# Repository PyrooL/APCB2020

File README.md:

# Advent of PCBs 2020
PCB design advent calendar: doing a design every [few] day[s]!

3 - RGB sensor using 3 photoresistors and filter paper, on an ATTiny85

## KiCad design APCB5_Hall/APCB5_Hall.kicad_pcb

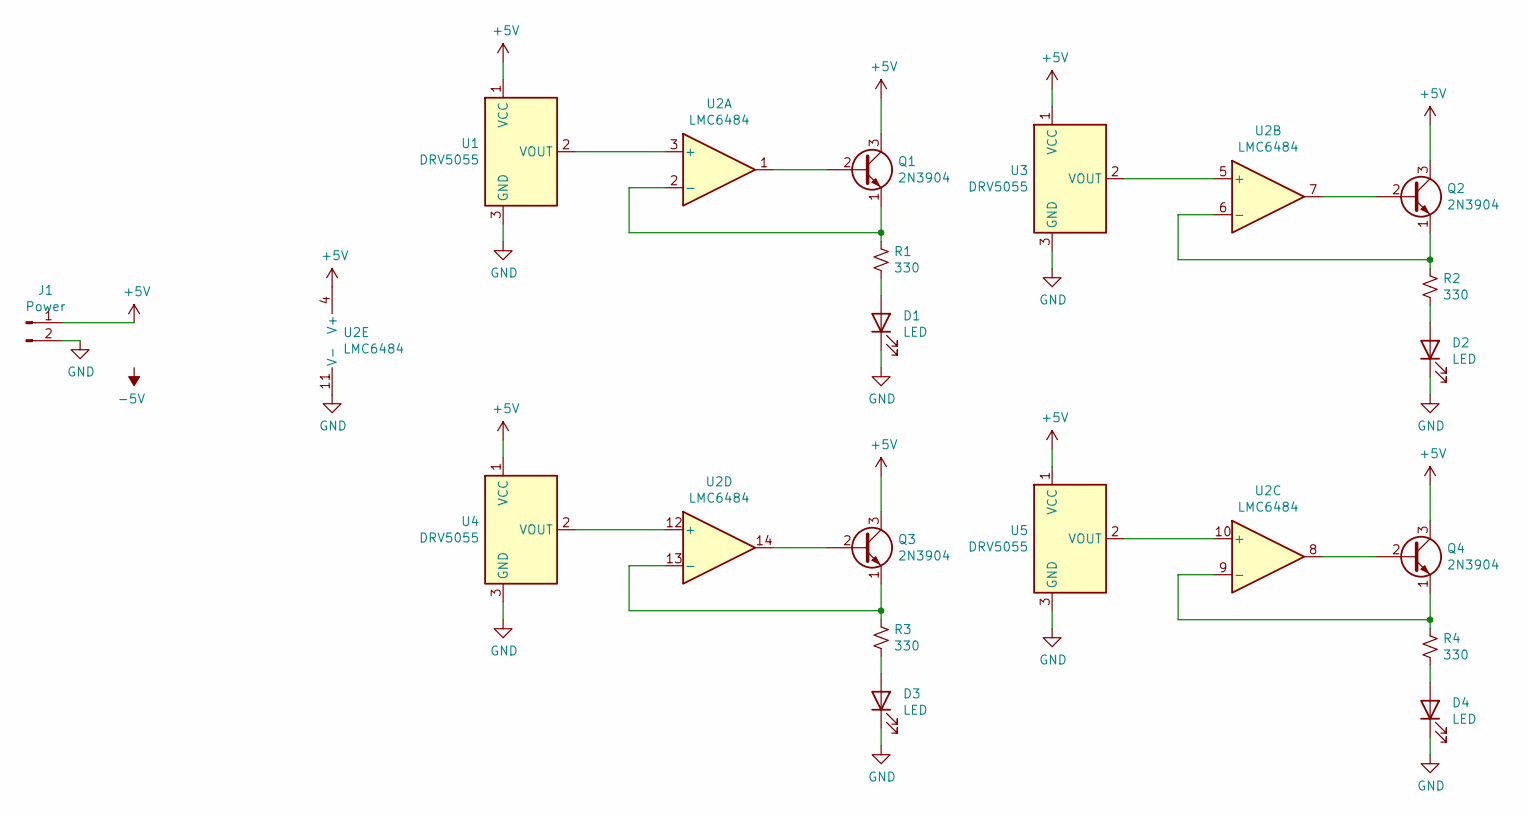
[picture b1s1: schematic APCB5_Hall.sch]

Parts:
D1, D2, D3, D4: LED; LED_1206_3216Metric
J1: Power; PinHeader_1x02_P2.54mm_Vertical
Q1, Q2, Q3, Q4: 2N3904; TO-92_Inline
R1, R2, R3, R4: 330; R_0805_2012Metric
U1, U3, U4, U5: DRV5055; SOT-23
U2: LMC6484; SOIC-14_3.9x8.7mm_P1.27mm

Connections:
+5V: J1.1, Q1.3 (C), Q2.3 (C), Q3.3 (C), Q4.3 (C), U1.1 (VCC), U2.4 (V+), U3.1 (VCC), U4.1 (VCC), U5.1 (VCC)
GND: D1.1 (K), D2.1 (K), D3.1 (K), D4.1 (K), J1.2, U1.3 (GND), U2.11 (V-), U3.3 (GND), U4.3 (GND), U5.3 (GND)
unnamed: D1.2 (A), R1.2
unnamed: D2.2 (A), R2.2
unnamed: D3.2 (A), R3.2
unnamed: D4.2 (A), R4.2
unnamed: Q1.1 (E), R1.1, U2.2 (-)
unnamed: Q1.2 (B), U2.1
unnamed: Q2.1 (E), R2.1, U2.6 (-)
unnamed: Q2.2 (B), U2.7
unnamed: Q3.1 (E), R3.1, U2.13 (-)
unnamed: Q3.2 (B), U2.14
unnamed: Q4.1 (E), R4.1, U2.9 (-)
unnamed: Q4.2 (B), U2.8
unnamed: U1.2 (VOUT), U2.3 (+)
unnamed: U2.5 (+), U3.2 (VOUT)
unnamed: U2.10 (+), U5.2 (VOUT)
unnamed: U2.12 (+), U4.2 (VOUT)

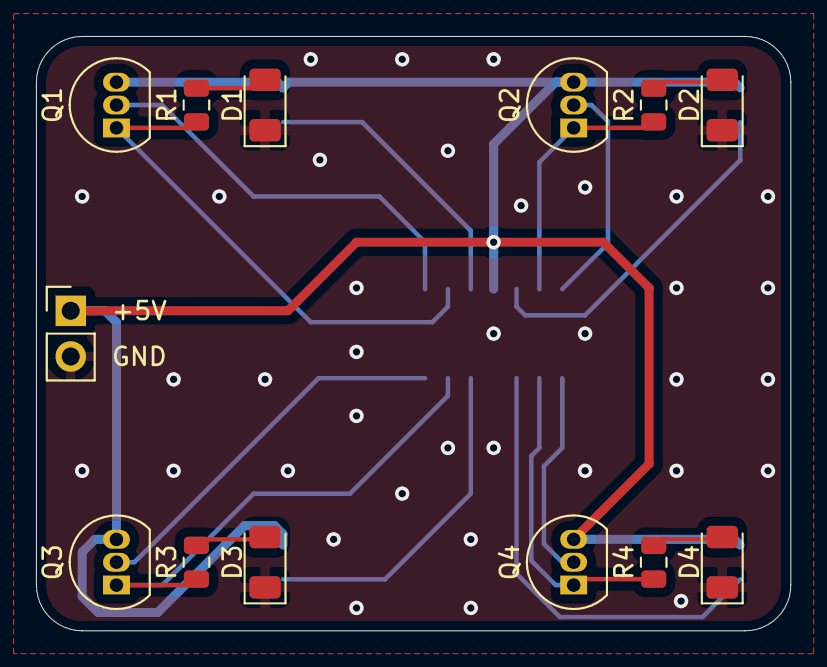
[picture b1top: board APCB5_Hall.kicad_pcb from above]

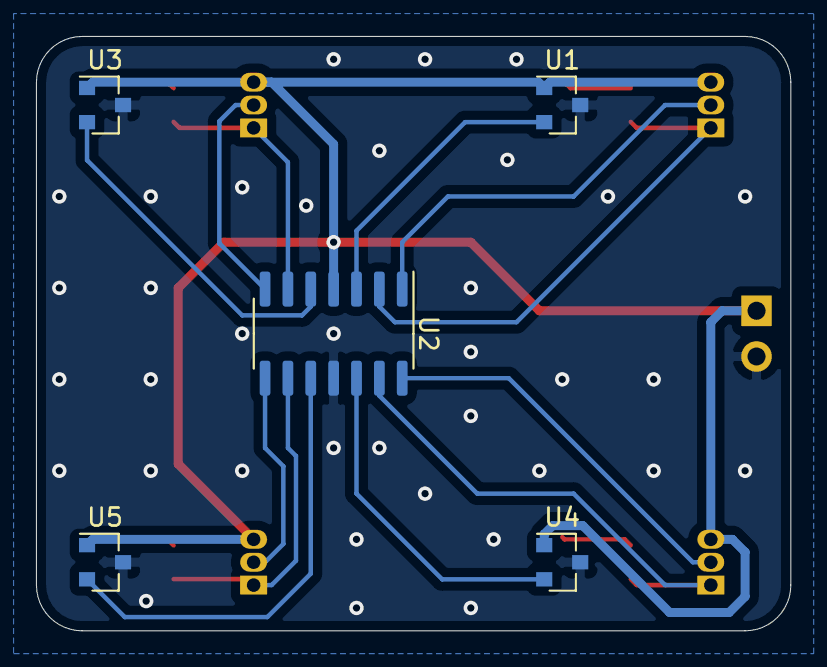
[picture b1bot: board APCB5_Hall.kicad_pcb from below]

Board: 2 copper layers, 41.9 x 33.0 mm, 18 parts (5 on the bottom side), 18 nets.

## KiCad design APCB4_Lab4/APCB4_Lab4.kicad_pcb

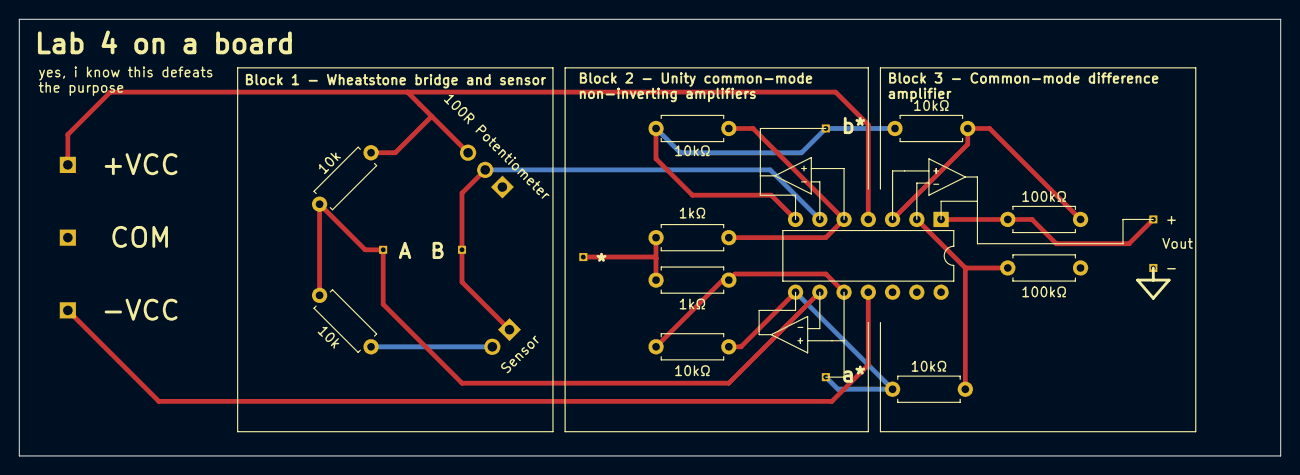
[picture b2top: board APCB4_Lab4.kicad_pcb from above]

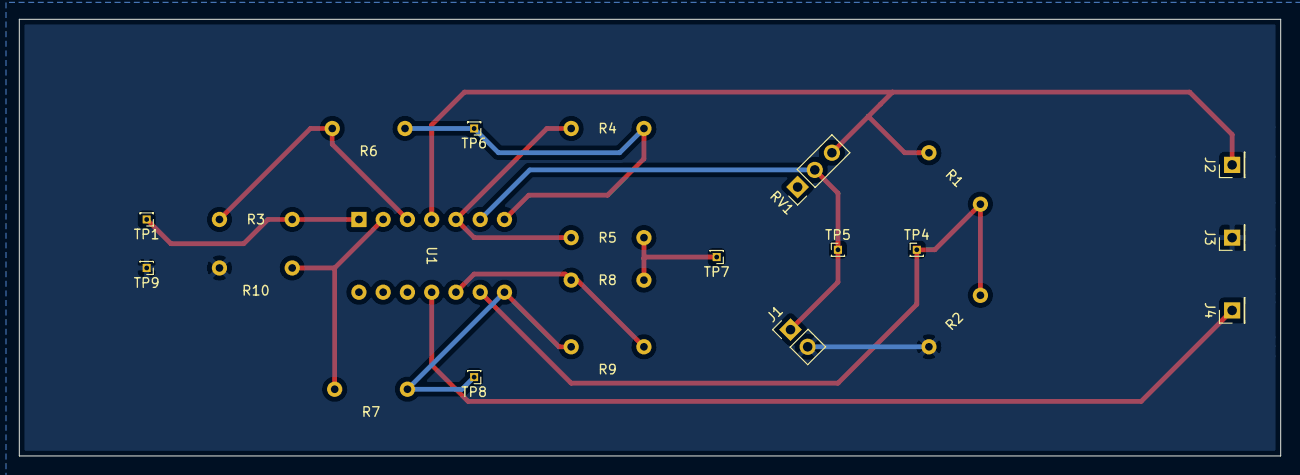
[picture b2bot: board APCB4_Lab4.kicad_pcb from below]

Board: 2 copper layers, 132.1 x 45.7 mm, 23 parts (12 on the bottom side), 13 nets.

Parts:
J1: Sensor; PinHeader_1x02_P2.54mm_Vertical
J2, J3, J4: Conn_01x01_Female; PinHeader_1x01_P2.54mm_Vertical
R1, R2: 10k; R_Axial_DIN0207_L6.3mm_D2.5mm_P7.62mm_Horizontal
R3, R10: 100kΩ; R_Axial_DIN0207_L6.3mm_D2.5mm_P7.62mm_Horizontal
R4, R6, R7, R9: 10kΩ; R_Axial_DIN0207_L6.3mm_D2.5mm_P7.62mm_Horizontal
R5, R8: 1kΩ; R_Axial_DIN0207_L6.3mm_D2.5mm_P7.62mm_Horizontal
RV1: 100R Potentiometer; PinHeader_1x03_P2.54mm_Vertical
TP1, TP4, TP5, TP6, TP7, TP8, TP9: TestPoint; PinHeader_1x01_P1.00mm_Vertical
U1: LMC6484; DIP-14_W7.62mm

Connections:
+VDC: J2.1, R1.1, RV1.3, U1.4
-VDC: J4.1, U1.11
/*: R5.1, R8.2, TP7.1
/A: R1.2, R2.1, TP4.1, U1.9
/B: J1.1, RV1.2, TP5.1, U1.6
/Vout: R3.2, TP1.1, U1.1
/a*: R7.2, R9.1, TP8.1, U1.8
/b*: R4.1, R6.2, TP6.1, U1.7
GND: J1.2, J3.1, R2.2, R10.1, TP9.1
unnamed: R3.1, R6.1, U1.3
unnamed: R4.2, R5.2, U1.5
unnamed: R8.1, R9.2, U1.10
unnamed: R7.1, R10.2, U1.2

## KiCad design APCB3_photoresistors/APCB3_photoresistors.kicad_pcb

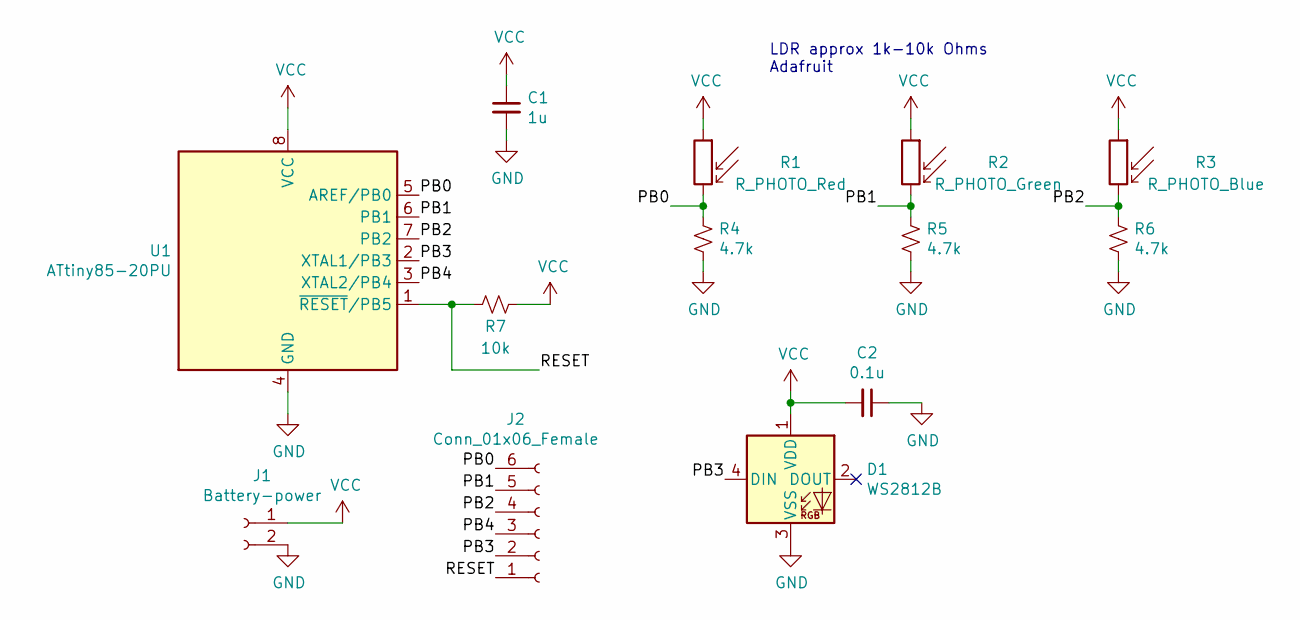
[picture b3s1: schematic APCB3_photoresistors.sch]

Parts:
C1: 1u; C_0805_2012Metric
C2: 0.1u; C_0805_2012Metric
D1: WS2812B; LED_WS2812B_PLCC4_5.0x5.0mm_P3.2mm
J1: Battery-power; PinHeader_1x02_P2.54mm_Vertical
J2: Conn_01x06_Female; PinHeader_1x06_P2.54mm_Vertical
R1: R_PHOTO_Red; R_LDR_5.1x4.3mm_P3.4mm_Vertical
R2: R_PHOTO_Green; R_LDR_5.1x4.3mm_P3.4mm_Vertical
R3: R_PHOTO_Blue; R_LDR_5.1x4.3mm_P3.4mm_Vertical
R4, R5, R6: 4.7k; R_0805_2012Metric
R7: 10k; R_0805_2012Metric
U1: ATtiny85-20PU; DIP-8_W7.62mm

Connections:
/PB0: J2.6, R1.2, R4.1, U1.5 (AREF/PB0)
/PB1: J2.5, R2.2, R5.1, U1.6 (PB1)
/PB2: J2.4, R3.2, R6.1, U1.7 (PB2)
/PB3: D1.4 (DIN), J2.2, U1.2 (XTAL1/PB3)
/PB4: J2.3, U1.3 (XTAL2/PB4)
/RESET: J2.1, R7.2, U1.1 (~RESET~/PB5)
GND: C1.2, C2.1, D1.3 (VSS), J1.2, R4.2, R5.2, R6.2, U1.4 (GND)
VCC: C1.1, C2.2, D1.1 (VDD), J1.1, R1.1, R2.1, R3.1, R7.1, U1.8 (VCC)

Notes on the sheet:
LDR approx 1k-10k Ohms Adafruit

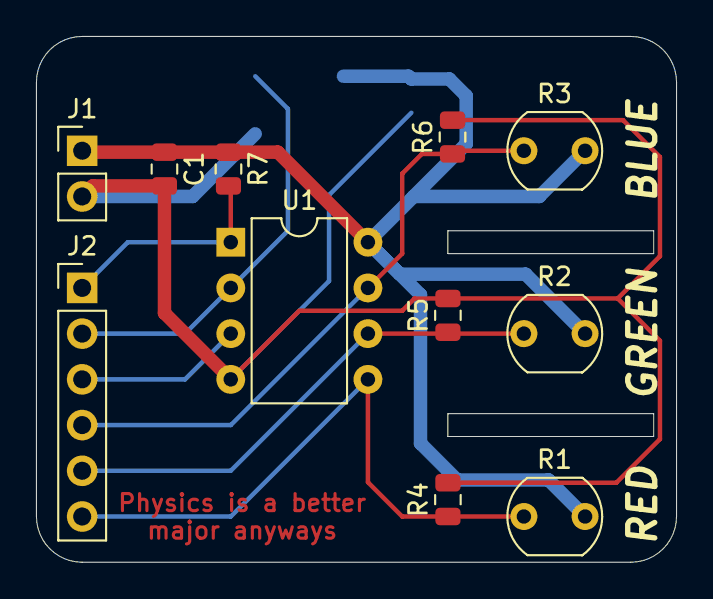
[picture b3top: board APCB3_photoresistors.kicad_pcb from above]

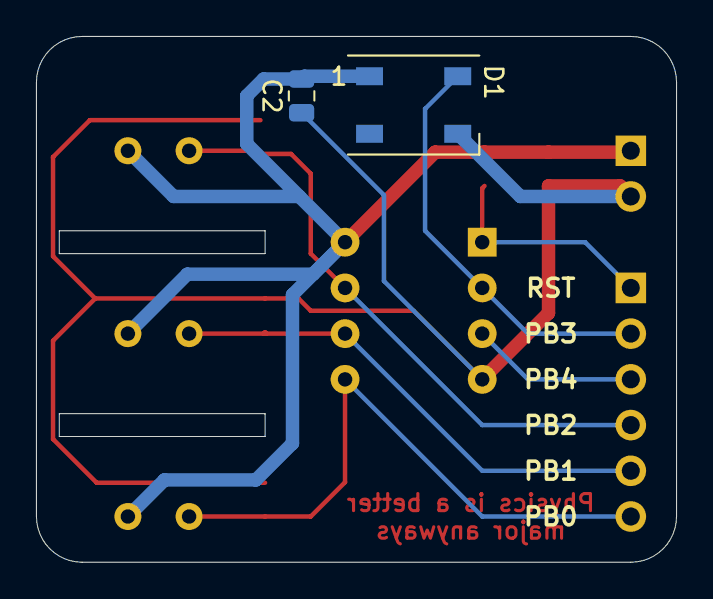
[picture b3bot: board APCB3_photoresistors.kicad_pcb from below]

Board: 2 copper layers, 35.6 x 29.2 mm, 13 parts (2 on the bottom side), 8 nets.

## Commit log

2020-12-03 APCB3
2020-12-06 Days 4 and 5
